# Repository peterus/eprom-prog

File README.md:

# EPROM Burner

Here you will find the circuit and the source code for a EPROM burner/programer.
This project can be used to program the famous 27/27Cxxx EPROM family.
With this circuit and software you will be able to write and read from an EPROM.

Additional to the provided hardware you will need a Arduino MEGA.
The provided circuit is easy to solder by our own with through hole components - no SMD soldering required!
I have some spare PCBs, you can contact me to get some.

## schematic

You can find the Eagle schematic in the 'schematic' folder.
Aditional you will need a Arduino MEGA board.

## source code

The source code can be found in the folder 'src', 'AVRhal' and some test-programs in 'test'.
The build system is cmake.

### compile

To compile the source code follow this steps:

   mkdir build && cd build
   cmake ..
   make
   
### flash the AVR/Arduino

   make upload_EPROM-PROG

## supported EPROMs

- 27C16 (not tested)
- 27C32 (not tested)
- 27C64 (not tested)
- 27C128 (not tested)
- 27C256 (not tested)
- 27C512 (not tested)
- 27C1001 (not tested)
- 27C2001 (not tested)
- 27C4001 (not tested)
- 27C801 (not tested)

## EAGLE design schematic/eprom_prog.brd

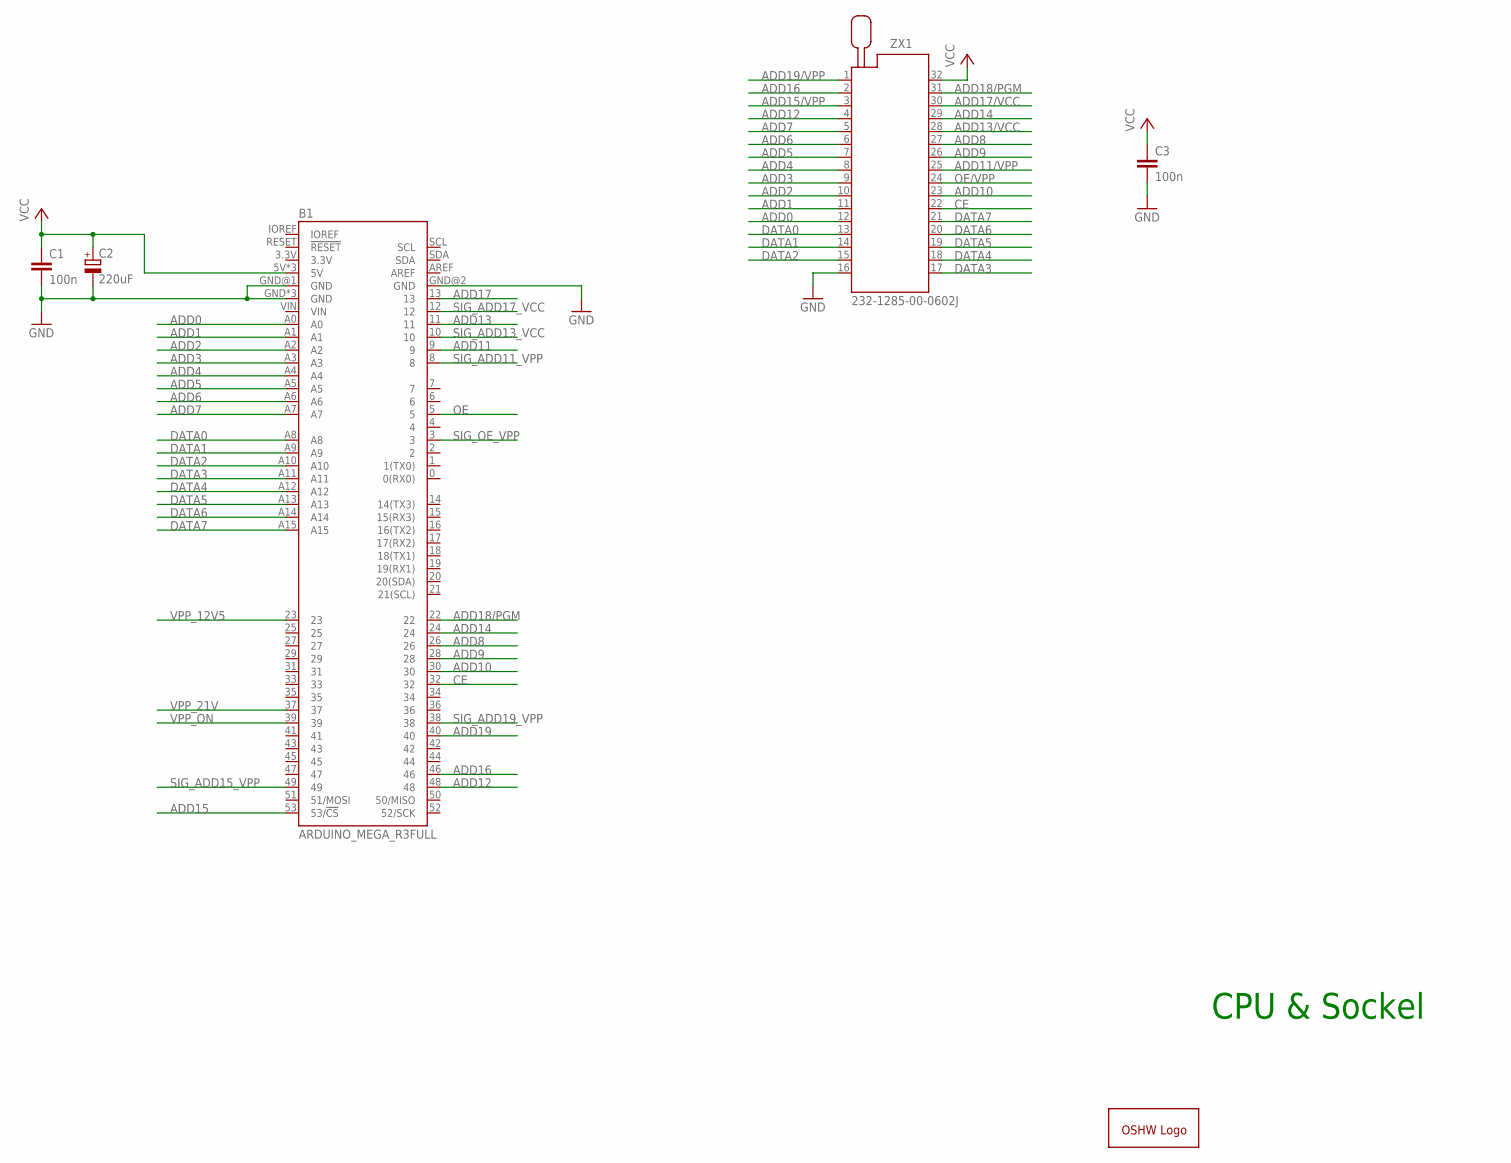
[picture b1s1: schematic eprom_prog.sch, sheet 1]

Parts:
B1: ARDUINO_MEGA_R3FULL; ARDUINO_MEGA_NO_SILK
C1, C3: 100n; C050-024X044
C2: 220uF; E2,5-6
GOLD_ORB_SM1: OSHWLOGOLOGO8MM; OSHW_8MM
ZX1: 232-1285-00-0602J

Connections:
ADD0: B1.A0, ZX1.12
ADD1: B1.A1, ZX1.11
ADD2: B1.A2, ZX1.10
ADD3: B1.A3, ZX1.9
ADD4: B1.A4, ZX1.8
ADD5: B1.A5, ZX1.7
ADD6: B1.A6, ZX1.6
ADD7: B1.A7, ZX1.5
ADD8: B1.26, ZX1.27
ADD9: B1.28, ZX1.26
ADD10: B1.30, ZX1.23
ADD11: B1.9; also elsewhere on the board
ADD11/VPP: ZX1.25; also elsewhere on the board
ADD12: B1.48, ZX1.4
ADD13: B1.11; also elsewhere on the board
ADD13/VCC: ZX1.28; also elsewhere on the board
ADD14: B1.24, ZX1.29
ADD15: B1.53 (53/!CS); also elsewhere on the board
ADD15/VPP: ZX1.3; also elsewhere on the board
ADD16: B1.46, ZX1.2
ADD17: B1.13; also elsewhere on the board
ADD17/VCC: ZX1.30; also elsewhere on the board
ADD18/PGM: B1.22, ZX1.31
ADD19: B1.40; also elsewhere on the board
ADD19/VPP: ZX1.1; also elsewhere on the board
CE: B1.32, ZX1.22
DATA0: B1.A8, ZX1.13
DATA1: B1.A9, ZX1.14
DATA2: B1.A10, ZX1.15
DATA3: B1.A11, ZX1.17
DATA4: B1.A12, ZX1.18
DATA5: B1.A13, ZX1.19
DATA6: B1.A14, ZX1.20
DATA7: B1.A15, ZX1.21
GND: B1.GND, B1.GND@1 (GND), B1.GND@2 (GND), B1.GND@3 (GND), B1.GND@4 (GND), C1.2, C2.-, C3.2, ZX1.16; also elsewhere on the board
OE: B1.5; also elsewhere on the board
OE/VPP: ZX1.24; also elsewhere on the board
SIG_ADD11_VPP: B1.8; also elsewhere on the board
SIG_ADD13_VCC: B1.10; also elsewhere on the board
SIG_ADD15_VPP: B1.49; also elsewhere on the board
SIG_ADD17_VCC: B1.12; also elsewhere on the board
SIG_ADD19_VPP: B1.38; also elsewhere on the board
SIG_OE_VPP: B1.3; also elsewhere on the board
VCC: B1.5V, B1.5V@1 (5V), B1.5V@2 (5V), C1.1, C2.+, C3.1, ZX1.32; also elsewhere on the board
VPP_12V5: B1.23; also elsewhere on the board
VPP_21V: B1.37; also elsewhere on the board
VPP_ON: B1.39; also elsewhere on the board

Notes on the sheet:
CPU & Sockel

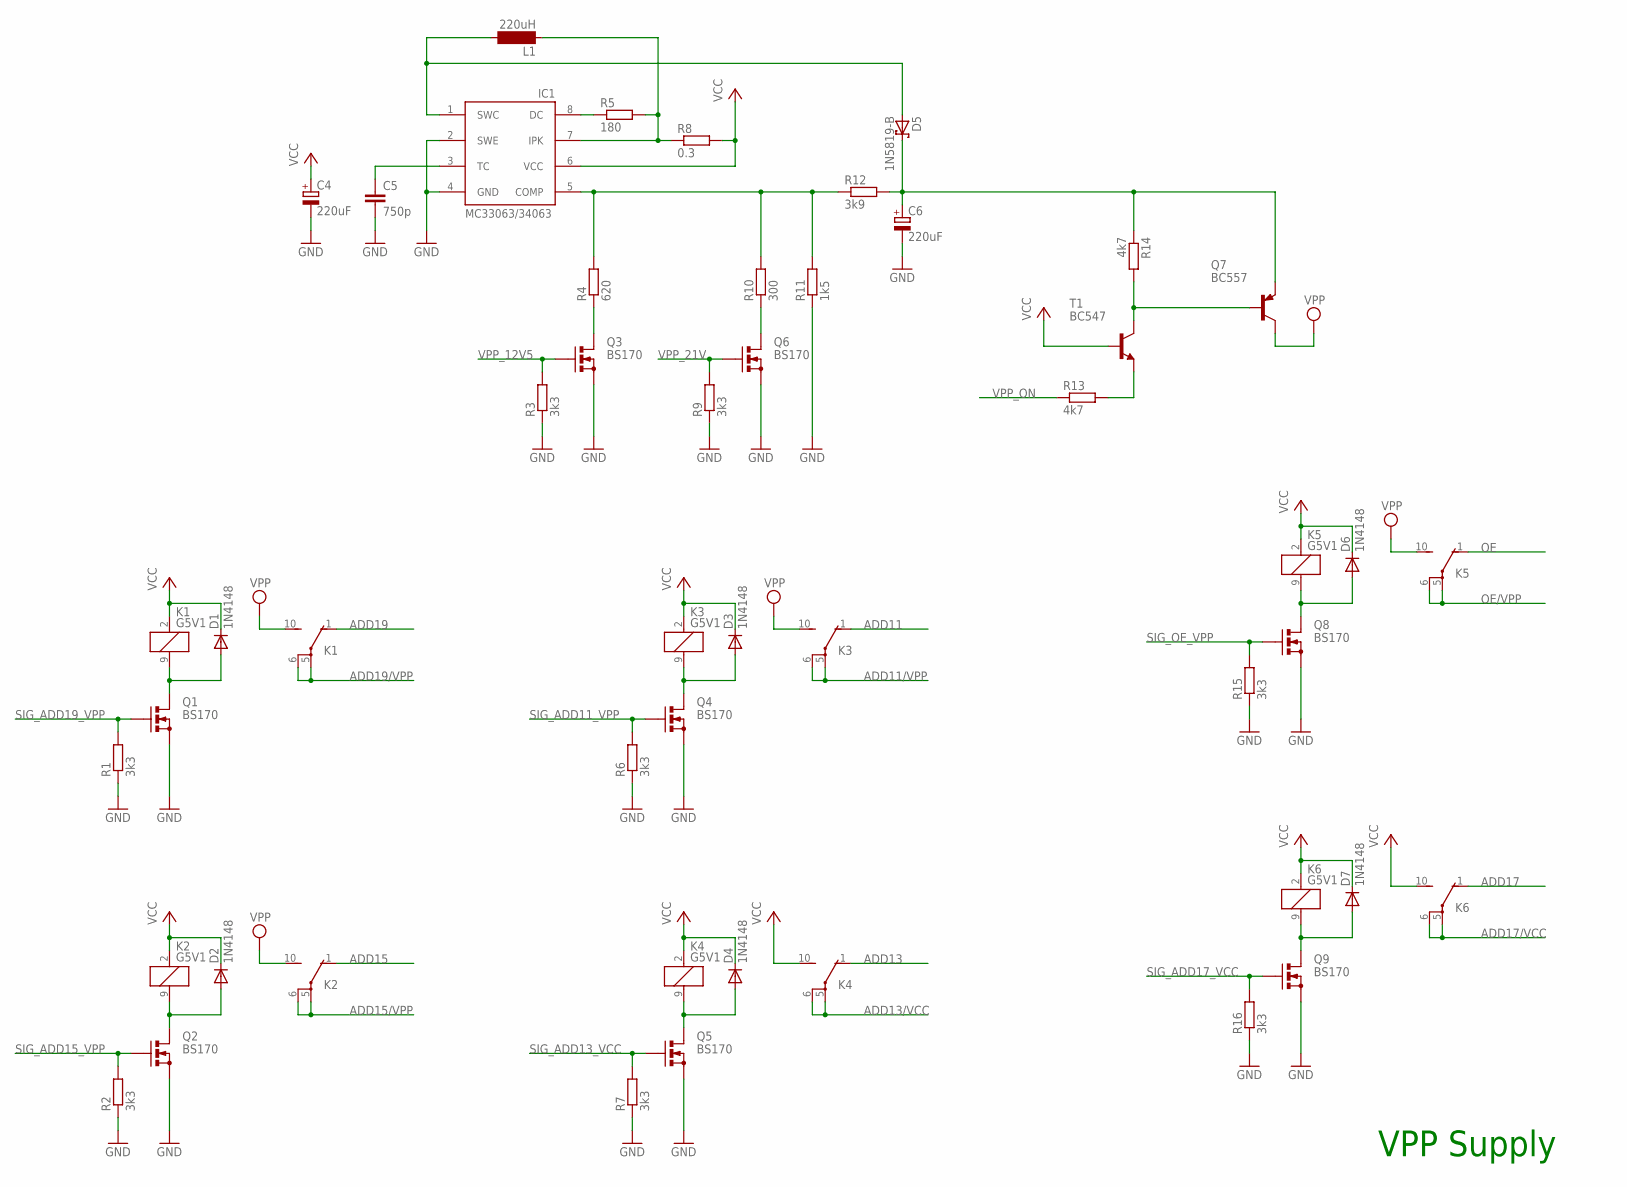
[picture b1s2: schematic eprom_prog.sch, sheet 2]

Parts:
C4, C6: 220uF; E2,5-6
C5: 750p; C050-024X044
D1, D2, D3, D4, D6, D7: 1N4148; DO35-7
D5: 1N5819-B; DO41-7.6
IC1: MC33063/MC34063P; DIL08
K1, K2, K3, K4, K5, K6: G5V1
L1: 220uH; SD12_1000
Q1, Q2, Q3, Q4, Q5, Q6, Q8, Q9: BS170; SOT54E
Q7: BC557; TO92
R1, R2, R3, R6, R7, R9, R15, R16: 3k3; 0207/2V
R4: 620; 0207/2V
R5: 180; 0207/2V
R8: 0.3; 0207/2V
R10: 300; 0207/2V
R11: 1k5; 0207/2V
R12: 3k9; 0207/2V
R13, R14: 4k7; 0207/2V
T1: BC547; TO92

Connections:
+VPP: C6.+, D5.C, Q7.1 (E), R12.2, R14.1
ADD11: K3.1 (O); also elsewhere on the board
ADD11/VPP: K3.5, K3.6; also elsewhere on the board
ADD13: K4.1 (O); also elsewhere on the board
ADD13/VCC: K4.5, K4.6; also elsewhere on the board
ADD15: K2.1 (O); also elsewhere on the board
ADD15/VPP: K2.5, K2.6; also elsewhere on the board
ADD17: K6.1 (O); also elsewhere on the board
ADD17/VCC: K6.5, K6.6; also elsewhere on the board
ADD19: K1.1 (O); also elsewhere on the board
ADD19/VPP: K1.5, K1.6; also elsewhere on the board
GND: C4.-, C5.2, C6.-, IC1.2 (SWE), IC1.4 (GND), Q1.S, Q2.S, Q3.S, Q4.S, Q5.S, Q6.S, Q8.S, Q9.S, R1.1, R2.1, R3.1, R6.1, R7.1, R9.1, R11.1, R15.1, R16.1; also elsewhere on the board
unnamed: D2.A, K2.9 (2), Q2.D
unnamed: IC1.7 (IPK), L1.1, R5.2, R8.1
unnamed: Q6.D, R10.1
unnamed: Q7.2 (B), R14.2, T1.3 (C)
unnamed: R13.2, T1.1 (E)
unnamed: Q3.D, R4.1
unnamed: C5.1, IC1.3 (TC)
unnamed: IC1.5 (COMP), R4.2, R10.2, R11.2, R12.1
unnamed: IC1.8 (DC), R5.1
unnamed: D5.A, IC1.1 (SWC), L1.2
unnamed: D1.A, K1.9 (2), Q1.D
unnamed: D3.A, K3.9 (2), Q4.D
unnamed: D4.A, K4.9 (2), Q5.D
unnamed: D6.A, K5.9 (2), Q8.D
unnamed: D7.A, K6.9 (2), Q9.D
OE: K5.1 (O); also elsewhere on the board
OE/VPP: K5.5, K5.6; also elsewhere on the board
SIG_ADD11_VPP: Q4.G, R6.2; also elsewhere on the board
SIG_ADD13_VCC: Q5.G, R7.2; also elsewhere on the board
SIG_ADD15_VPP: Q2.G, R2.2; also elsewhere on the board
SIG_ADD17_VCC: Q9.G, R16.2; also elsewhere on the board
SIG_ADD19_VPP: Q1.G, R1.2; also elsewhere on the board
SIG_OE_VPP: Q8.G, R15.2; also elsewhere on the board
VCC: C4.+, D1.C, D2.C, D3.C, D4.C, D6.C, D7.C, IC1.6 (VCC), K1.2 (1), K2.2 (1), K3.2 (1), K4.2 (1), K4.10 (S), K5.2 (1), K6.2 (1), K6.10 (S), R8.2, T1.2 (B); also elsewhere on the board
VPP: K1.10 (S), K2.10 (S), K3.10 (S), K5.10 (S), Q7.3 (C)
VPP_12V5: Q3.G, R3.2; also elsewhere on the board
VPP_21V: Q6.G, R9.2; also elsewhere on the board
VPP_ON: R13.1; also elsewhere on the board

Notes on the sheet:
VPP Supply

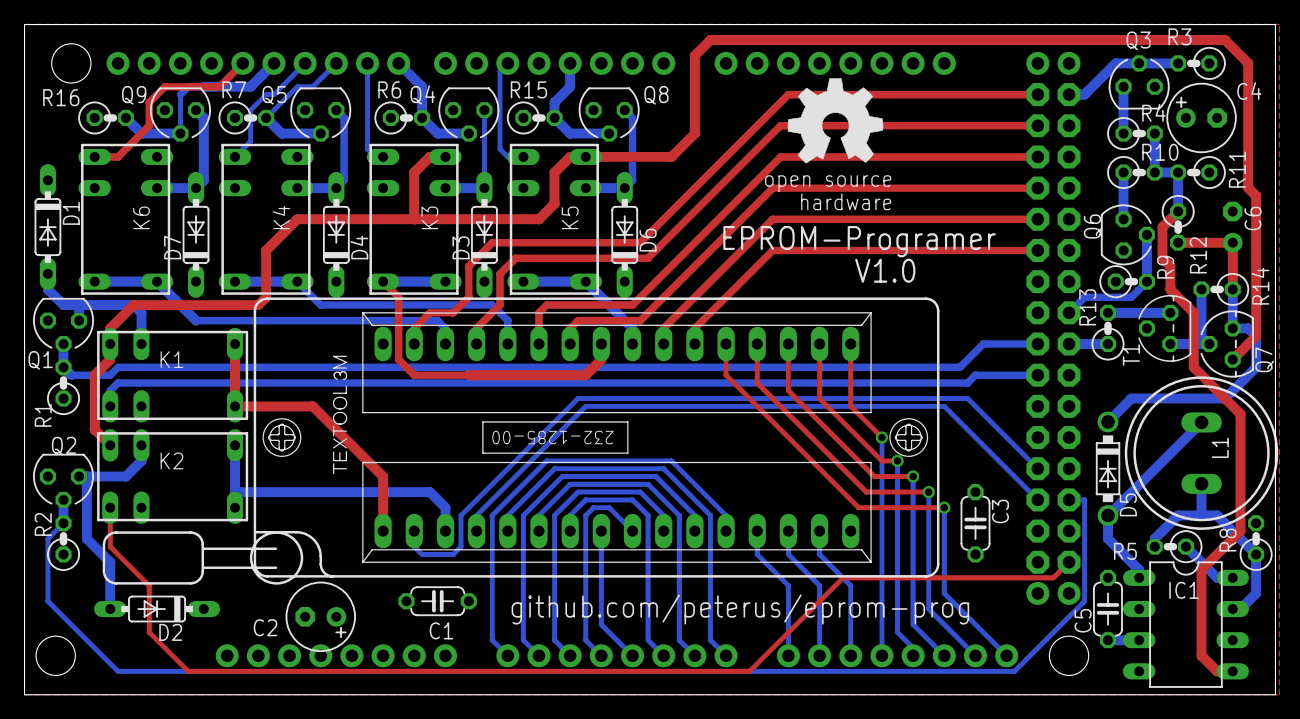
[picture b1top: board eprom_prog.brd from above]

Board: 2 copper layers, 101.9 x 54.6 mm, 50 parts (1 on the bottom side), 64 nets.

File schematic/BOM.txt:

Stückliste exportiert aus /home/pbuchegger/project/eprom-prog/schematic/eprom_prog.sch am 16.04.19 19:44

Part         Value               Device              Package              Description                          MF MPN               OC_FARNELL OC_NEWARK
B1           ARDUINO_MEGA_R3FULL ARDUINO_MEGA_R3FULL ARDUINO_MEGA_NO_SILK Arduino Mega R3                                                               
C1           100n                C-EU050-024X044     C050-024X044         CAPACITOR, European symbol                                                    
C2           220uF               CPOL-EUE2.5-6       E2,5-6               POLARIZED CAPACITOR, European symbol                                          
C3           100n                C-EU050-024X044     C050-024X044         CAPACITOR, European symbol                                                    
C4           220uF               CPOL-EUE2.5-6       E2,5-6               POLARIZED CAPACITOR, European symbol                                          
C5           750p                C-EU050-024X044     C050-024X044         CAPACITOR, European symbol                                                    
C6           220uF               CPOL-EUE2.5-6       E2,5-6               POLARIZED CAPACITOR, European symbol                                          
D1           1N4148              1N4148DO35-7        DO35-7               DIODE                                                                         
D2           1N4148              1N4148DO35-7        DO35-7               DIODE                                                                         
D3           1N4148              1N4148DO35-7        DO35-7               DIODE                                                                         
D4           1N4148              1N4148DO35-7        DO35-7               DIODE                                                                         
D5           1N5819-B            1N5819-B            DO41-7.6             1.0A SCHOTTKY BARRIER RECTIFIER                                               
D6           1N4148              1N4148DO35-7        DO35-7               DIODE                                                                         
D7           1N4148              1N4148DO35-7        DO35-7               DIODE                                                                         
GOLD_ORB_SM1 OSHWLOGOLOGO8MM     OSHWLOGOLOGO8MM     OSHW_8MM             The OSHW logo for PCB layout                                                  
IC1          MC33063/MC34063P    MC33063/MC34063P    DIL08                MC33063 and MC34063                                                           
K1           G5V1                G5V1                G5V1                 RELAY                                   G5V-1-DC24        9949593    36M6377  
K2           G5V1                G5V1                G5V1                 RELAY                                   G5V-1-DC24        9949593    36M6377  
K3           G5V1                G5V1                G5V1                 RELAY                                   G5V-1-DC24        9949593    36M6377  
K4           G5V1                G5V1                G5V1                 RELAY                                   G5V-1-DC24        9949593    36M6377  
K5           G5V1                G5V1                G5V1                 RELAY                                   G5V-1-DC24        9949593    36M6377  
K6           G5V1                G5V1                G5V1                 RELAY                                   G5V-1-DC24        9949593    36M6377  
L1           220uH               SD12-1000           SD12_1000            INDUCTOR                                                  unknown    unknown  
Q1           BS170               BS170               SOT54E               N-CHANNEL MOS FET                                                             
Q2           BS170               BS170               SOT54E               N-CHANNEL MOS FET                                                             
Q3           BS170               BS170               SOT54E               N-CHANNEL MOS FET                                                             
Q4           BS170               BS170               SOT54E               N-CHANNEL MOS FET                                                             
Q5           BS170               BS170               SOT54E               N-CHANNEL MOS FET                                                             
Q6           BS170               BS170               SOT54E               N-CHANNEL MOS FET                                                             
Q7           BC557               BC557               TO92                 PNP Transistor                                                                
Q8           BS170               BS170               SOT54E               N-CHANNEL MOS FET                                                             
Q9           BS170               BS170               SOT54E               N-CHANNEL MOS FET                                                             
R1           3k3                 R-EU_0207/2V        0207/2V              RESISTOR, European symbol                                                     
R2           3k3                 R-EU_0207/2V        0207/2V              RESISTOR, European symbol                                                     
R3           3k3                 R-EU_0207/2V        0207/2V              RESISTOR, European symbol                                                     
R4           620                 R-EU_0207/2V        0207/2V              RESISTOR, European symbol                                                     
R5           180                 R-EU_0207/2V        0207/2V              RESISTOR, European symbol                                                     
R6           3k3                 R-EU_0207/2V        0207/2V              RESISTOR, European symbol                                                     
R7           3k3                 R-EU_0207/2V        0207/2V              RESISTOR, European symbol                                                     
R8           0.3                 R-EU_0207/2V        0207/2V              RESISTOR, European symbol                                                     
R9           3k3                 R-EU_0207/2V        0207/2V              RESISTOR, European symbol                                                     
R10          300                 R-EU_0207/2V        0207/2V              RESISTOR, European symbol                                                     
R11          1k5                 R-EU_0207/2V        0207/2V              RESISTOR, European symbol                                                     
R12          3k9                 R-EU_0207/2V        0207/2V              RESISTOR, European symbol                                                     
R13          4k7                 R-EU_0207/2V        0207/2V              RESISTOR, European symbol                                                     
R14          4k7                 R-EU_0207/2V        0207/2V              RESISTOR, European symbol                                                     
R15          3k3                 R-EU_0207/2V        0207/2V              RESISTOR, European symbol                                                     
R16          3k3                 R-EU_0207/2V        0207/2V              RESISTOR, European symbol                                                     
T1           BC547               BC547               TO92                 NPN TRANSISTOR                                                                
ZX1          232-1285-00-0602J   232-1285-00-0602J   232-1285-00-0602J    Zero Insertion Force Socked          3M 232-1285-00-0602J 9897402    85K7839

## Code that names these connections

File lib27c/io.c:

#include "GPIO/GPIO.h"

gpio_map_t data_map = {
	.size = 8,
	.gpio = { &gpio[ePORTK][0], &gpio[ePORTK][1], &gpio[ePORTK][2], &gpio[ePORTK][3], &gpio[ePORTK][4], &gpio[ePORTK][5], &gpio[ePORTK][6], &gpio[ePORTK][7] }
};

gpio_map_t address_map = {
	.size = 20,
	.gpio = { 
		&gpio[ePORTF][0],
		&gpio[ePORTF][1],
		&gpio[ePORTF][2],
		&gpio[ePORTF][3],
		&gpio[ePORTF][4],
		&gpio[ePORTF][5],
		&gpio[ePORTF][6],
		&gpio[ePORTF][7], // ADD7
		&gpio[ePORTA][4], // ADD8
		&gpio[ePORTA][6], // ADD9
		&gpio[ePORTC][7], // ADD10
		&gpio[ePORTH][6], // ADD11
		&gpio[ePORTL][1], // ADD12
		&gpio[ePORTB][5], // ADD13
		&gpio[ePORTA][2], // ADD14
		&gpio[ePORTB][0], // ADD15
		&gpio[ePORTL][3], // ADD16
		&gpio[ePORTB][7], // ADD17
		&gpio[ePORTA][0], // ADD18 / PGM
		&gpio[ePORTG][1], // ADD19
	}
};

gpio_t * vpp_12v5_pin = &gpio[ePORTA][1];
gpio_t * vpp_21v_pin  = &gpio[ePORTC][0];
gpio_t * vpp_on_pin   = &gpio[ePORTG][2];

gpio_t * sig_oe_vpp_pin    = &gpio[ePORTE][5];
gpio_t * sig_add11_vpp_pin = &gpio[ePORTH][5];
gpio_t * sig_add13_vcc_pin = &gpio[ePORTB][4];
gpio_t * sig_add15_vpp_pin = &gpio[ePORTL][0];
gpio_t * sig_add17_vcc_pin = &gpio[ePORTB][6];
gpio_t * sig_add19_vpp_pin = &gpio[ePORTD][7];

gpio_t * CE_pin  = &gpio[ePORTC][5];
gpio_t * OE_pin  = &gpio[ePORTE][3];
gpio_t * PGM_pin = &gpio[ePORTA][0];


void reset_all(void)
{
	set_input_map(&data_map);
	set_output_map(&address_map);

	set_output(vpp_on_pin);
	set_output(vpp_12v5_pin);
	set_output(vpp_21v_pin);

	set_output(sig_oe_vpp_pin);
	set_output(sig_add11_vpp_pin);
	set_output(sig_add13_vcc_pin);
	set_output(sig_add15_vpp_pin);
	set_output(sig_add17_vcc_pin);
	set_output(sig_add19_vpp_pin);

	set_output(CE_pin);
	set_output(OE_pin);
	set_output(PGM_pin);

	set_pins_map(&address_map, 0);

	set_high(vpp_on_pin);
	set_low(vpp_12v5_pin);
	set_low(vpp_21v_pin);

	set_low(sig_oe_vpp_pin);
	set_low(sig_add11_vpp_pin);
	set_low(sig_add13_vcc_pin);
	set_low(sig_add15_vpp_pin);
	set_low(sig_add17_vcc_pin);
	set_low(sig_add19_vpp_pin);

	set_low(CE_pin);
	set_low(OE_pin);
	set_low(PGM_pin);
}

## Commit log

2019-04-16 first upload
2019-04-16 schematic: BOM and pdf export
2019-04-16 AVRhal added
2019-04-16 cmake working
2019-04-16 Set theme jekyll-theme-slate
2019-04-18 working CMake env.
2019-04-28 first test
2019-04-29 basic test for VPP added
2019-05-05 first working firmware
2019-05-25 first working fw
2019-05-25 reorder folders and source
2019-05-25 added binary functions and python code
2019-05-28 first working read, but very slow hints: - boud rate - size of bytes to transfer
2019-05-29 working now for different 27c*** - added some test files - python script updated for write - faster read

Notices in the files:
parts and their libraries:
SparkFun-Boards: Licensing: Creative Commons ShareAlike 4.0 International - https://creativecommons.org/licenses/by-sa/4.0
